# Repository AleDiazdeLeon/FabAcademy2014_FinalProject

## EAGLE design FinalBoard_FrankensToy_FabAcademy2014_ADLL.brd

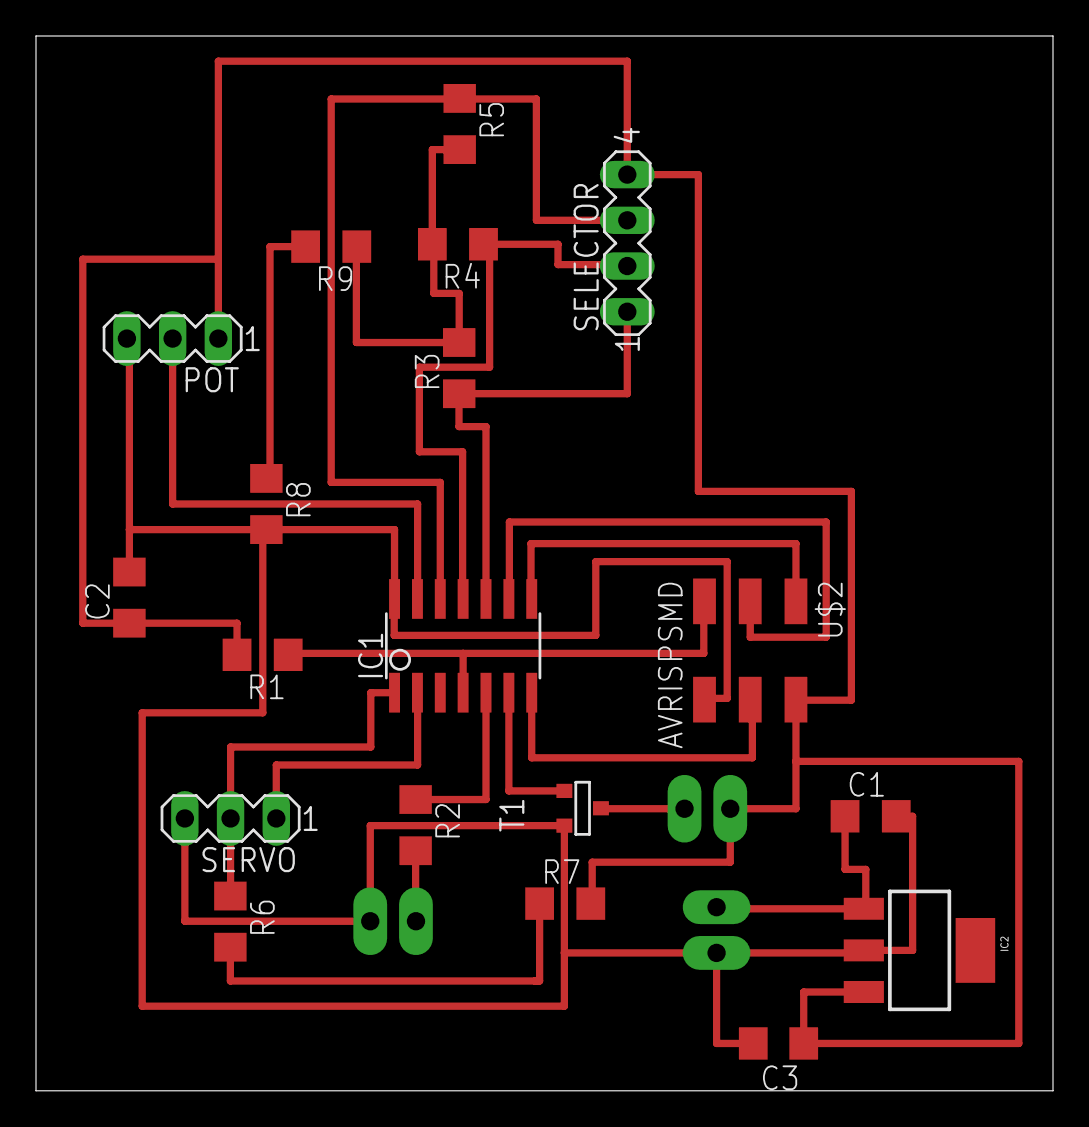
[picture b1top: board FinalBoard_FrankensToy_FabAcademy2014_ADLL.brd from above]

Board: 2 copper layers, 56.5 x 58.6 mm, 22 parts (0 on the bottom side), 18 nets.

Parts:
C1: .47uf; 1206
C2: 1uf; 1206
C3: 22uf; C1206
IC1: ATTINY44-SSU; SOIC14
IC2: SOT223
LED: 1X02_LONGPADS
POT: MA03-1
POWER: 1X02_LONGPADS
R1, R3, R4, R5: 10k; R1206
R2: 499; 1206
R6, R7, R8, R9: 0k; 1206
SELECTOR: MA04-1
SERVO: MA03-1
SPEAK: 1X02_LONGPADS
T1: SOT-23
U$2: AVRISPSMD; 2X03SMD

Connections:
5V: C2.1, C3.1, IC1.1, IC2.OUT, POT.1, R1.2, R6.1, R7.2, SELECTOR.4, SERVO.2, SPEAK.2, U$2.2
GND: C1.2, C2.2, C3.2, IC1.14, IC2.GNDSM, LED.2, POT.3, POWER.1, R3.2, R4.2, R5.2, R8.2, SERVO.3, T1.2, U$2.6
MISO: IC1.8, U$2.1
MOSI: IC1.7, U$2.4
unnamed: IC1.5, R2.1
unnamed: SPEAK.1, T1.1
unnamed: R6.2, R7.1
unnamed: LED.1, R2.2
unnamed: R8.1, R9.2
PINSPEAK: IC1.6, T1.3
RST: IC1.4, R1.1, U$2.5
SCK: IC1.9, U$2.3
SEL1: IC1.10, R3.1, SELECTOR.1
SEL2: IC1.11, R4.1, SELECTOR.2
SEL3: IC1.12, R5.1, SELECTOR.3
SERVO: IC1.2, SERVO.1
TX: IC1.13, POT.2
VCC: C1.1, IC2.IN, POWER.2

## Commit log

2014-06-16 Final Project "FrankensToy"Final files

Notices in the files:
parts and their libraries:
01_SparkFun: Licensing: CC v3.0 Share-Alike You are welcome to use this library for commercial purposes.
